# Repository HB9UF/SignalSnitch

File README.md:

# HB9UF SignalSnitch

## Introduction

At the [Fantasy Basel](https://fantasybasel.ch) 2025, we were thrilled to participate with a booth, sharing the space with [AMSAT-HB](//www.amsat-hb.org/) in the section of the [Swiss Space Museum](https://swissspacemuseum.ch/). As part of our contribution to this unique blend of science, pop culture, and hands-on experiences, we introduced the SignalSnitch -- a simple, educational RF detector kit designed by Andreas HB9HDF.

The SignalSnitch kit was created specifically for this event to spark interest in amateur radio through a hands-on activity that anyone could enjoy. The kit uses through-hole technology (THT) components to keep assembly straightforward and beginner-friendly, making it ideal for both newcomers and seasoned enthusiasts. Once put together, it lights up an LED when it detects the presence of a nearby RF signal, offering a tangible and satisfying introduction to radio frequency detection.

The concept behind SignalSnitch is not entirely new -- it builds upon a [similar kit with SMD parts](https://github.com/HB9UF/aufdermauer/) conceived by Hansjörg HB9DWS and implemented by Matt HB9FRV for the 2019 HAMFEST in Zug.

The response was overwhelmingly positive! We had a fantastic time meeting fellow hobbyists, curious newcomers, and future radio amateurs. We were out of kits long before the fare ended. A heartfelt thank you to everyone who helped make this project possible and to all who stopped by to build their own SignalSnitch. Your enthusiasm made this experience truly memorable.

## Schematic and Theory of Operation

This simple circuit works as follows: The PCB antenna picks up electromagnetic fields, in consequence, AC voltage develops across the antenna terminals. Diodes `D1` and `D2` rectify this AC voltage to a DC voltage across capacitor `C1`. This DC voltage activates JFET `Q1` which in turn enables `Q2`. Light is emitted by LED `D3` due to the resulting collector current. Bias can be adjusted with `Pot1`.

## PCB
The PCB features the schematic on the front side and a QR code for [assembly instructions](https://hb9uf.ch/snitch). Components are clearly labeled and assembly is straight forward. See below for images of the board as well as a video of the kit in operation.

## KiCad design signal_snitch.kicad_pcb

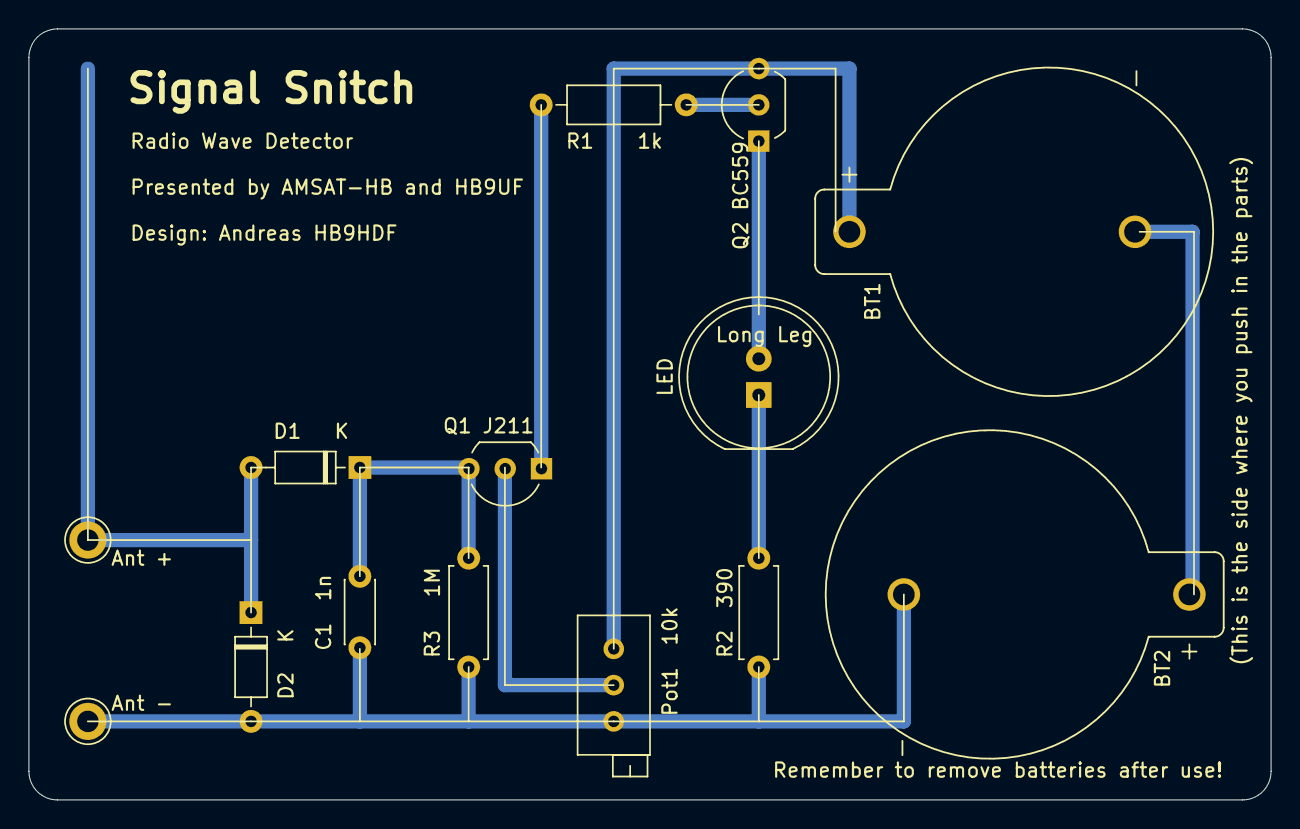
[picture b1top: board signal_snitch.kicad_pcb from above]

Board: 2 copper layers, 87.0 x 54.0 mm, 14 parts (0 on the bottom side), 8 nets.

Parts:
Ant +: Pin_D1.3mm_L11.0mm
Ant -: Pin_D1.3mm_L11.0mm
BT1, BT2: CR2032; BAT_1066
C1  1n: 1n; C_Disc_D4.3mm_W1.9mm_P5.00mm
D1, D2: 1N5711; D_DO-35_SOD27_P7.62mm_Horizontal
LED: LED 10MM; LED_D10.0mm
Pot1  10k: 10k; Potentiometer_Bourns_3296X_Horizontal
Q1 J211: TO-92_Inline_Wide
Q2 BC559: BC559; TO-92_Inline_Wide
R1    1k: 1k; R_Axial_DIN0207_L6.3mm_D2.5mm_P10.16mm_Horizontal
R2  390: 390; R_Axial_DIN0207_L6.3mm_D2.5mm_P7.62mm_Horizontal
R3   1M: 1M; R_Axial_DIN0207_L6.3mm_D2.5mm_P7.62mm_Horizontal

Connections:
GND: BT2.N, C1 1n.2, D2.2 (A), Pot1 10k.3, R2 390.1, R3 1M.2
unnamed: D1.2 (A), D2.1 (K)
unnamed: BT1.N, BT2.P
unnamed: C1 1n.1, D1.1 (K), R3 1M.1
unnamed: LED.2 (A), Q2 BC559.1 (C)
unnamed: LED.1 (K), R2 390.2
unnamed: Q2 BC559.2 (B), R1 1k.2
unnamed: BT1.P, Pot1 10k.1, Q2 BC559.3 (E)

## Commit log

2025-05-30 Initial version of KiCad project as designed by HB9HDF
2025-05-30 Offset R1 designator in schematic to avoid overlaps
2025-05-30 PNG for schematic (to be included in README)
2025-05-30 Initial version of README.md file
2025-05-31 Adding 2D renders to README and contrib/
